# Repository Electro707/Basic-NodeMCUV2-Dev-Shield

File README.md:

# E707 Basic NodeMCU-V2 Shield 

This shield/daughterboard is for the NodeMCU V2 (also known as NodeMCU DevKit V1.0, kind of confusing) to allow a begineer to have some components to play around with. In this case, that includes a 7-segment display, an RGB LED (which is hooked up with the 7-segment display), and 3 pushbuttons.

### Arduino Library

The Arduino library for this shield can be found at: [https://github.com/Electro707/Basic-NodeMCUV2-Dev-Shield-Library](https://github.com/Electro707/Basic-NodeMCUV2-Dev-Shield-Library). It provides pin definitions and more importantly some examples to get started with.

The reason it's in a different repo is to allow for an easy download of the library as a ZIP file (using GitHub's "Download ZIP" option) to be easily imported into the Arduino IDE. 

### PCB

The PCB files can be found in the `KiCAD Files` folder. 

There are different folders for different PCB layouts. More details can be found in [KiCAD_Files/README.md](KiCAD_Files/README.md)

#### PCB Panel

There is a panel (not tested tough) of the PCB for mass-production:

##### NOTE: If you have KiCAD 5.1.9 or lower, the KiCAD files will not open as it was designed with KiCAD 5.99 (the alpha/beta version of KiCAD V6).

### Docs 
Coming Soon!

### Credits:
- Creator and Maintainer:
    - Electro707 (Jamal Bouajjaj)
- KiCAD NODEMCU V2 Symbol:
    - jdunmire -> [https://github.com/jdunmire/kicad-ESP8266](https://github.com/jdunmire/kicad-ESP8266)
- Some Icons:
    - Arduino's IDE Repo -> [https://github.com/arduino/Arduino/blob/master/build/shared/lib/theme/buttons.svg](https://github.com/arduino/Arduino/blob/master/build/shared/lib/theme/buttons.svg)

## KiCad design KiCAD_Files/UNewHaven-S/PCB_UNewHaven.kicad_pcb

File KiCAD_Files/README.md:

# KiCAD Files Versions

There are different folders in this directory, and they are different versions of this shield. The schematic is all the same, the difference lying in the PCB layout/footprints.

- Standard-S: The regular SMD version of the board, optimized for mass production.
- Standard-T: The regular THT version of the board, optimized to be used as a soldering kit.
- UNewHaven-S: The University of New Haven version, used for the school's "Welcome Kit" something. Optimized for mass production.

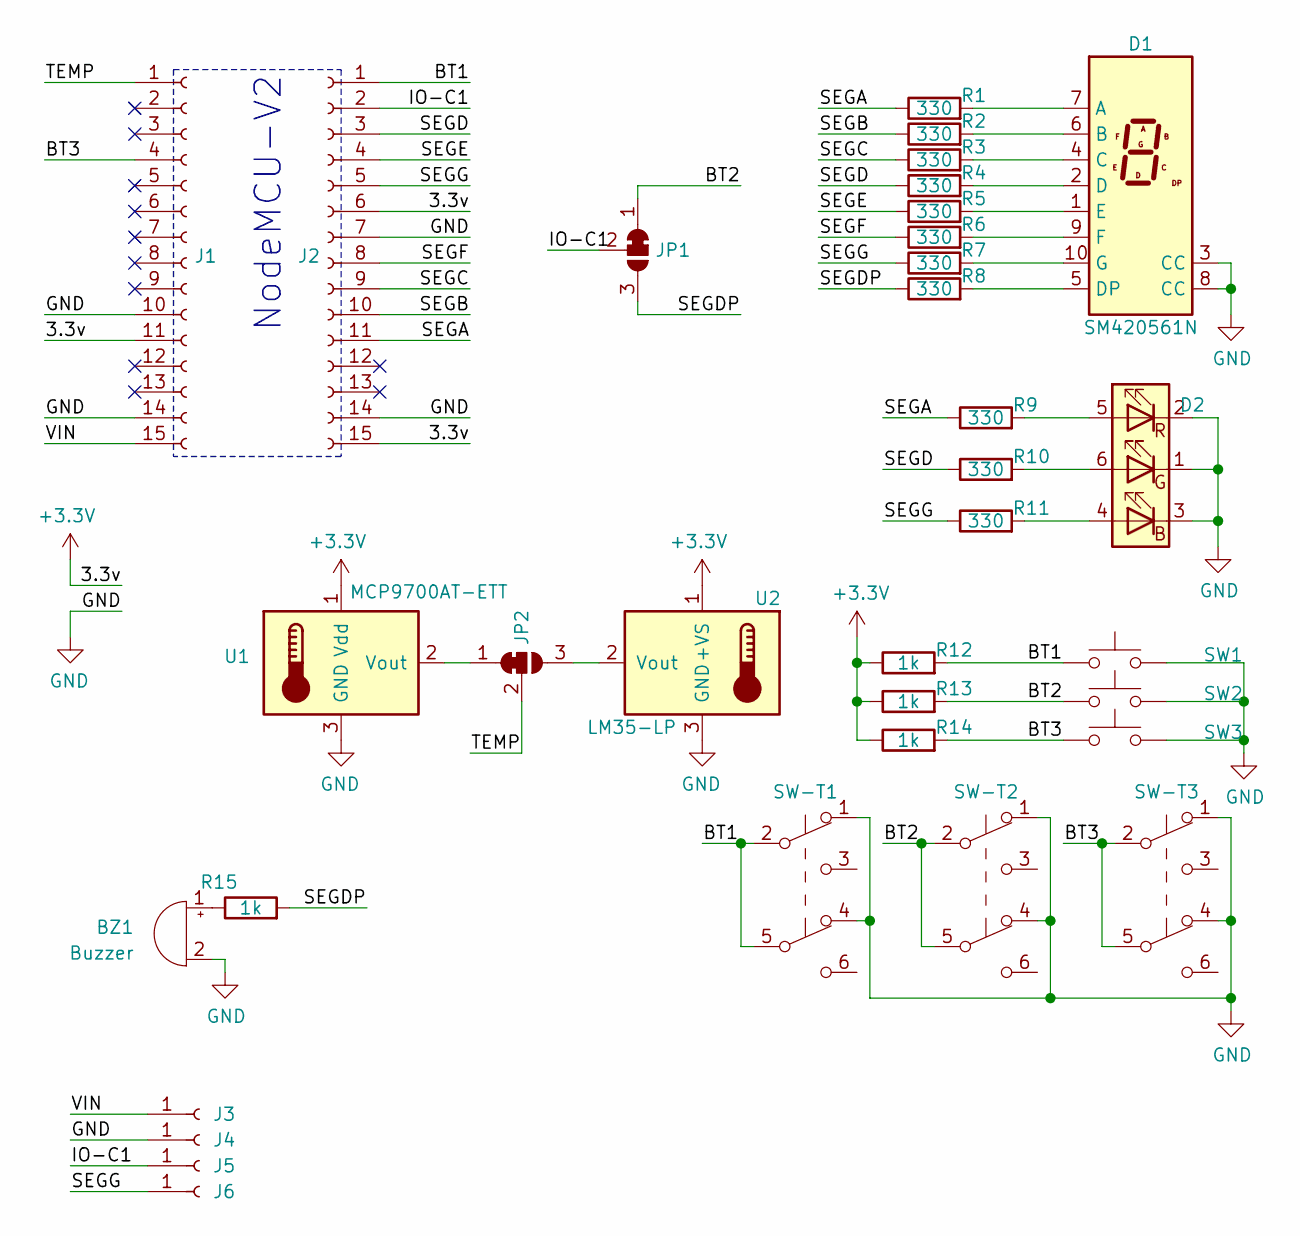
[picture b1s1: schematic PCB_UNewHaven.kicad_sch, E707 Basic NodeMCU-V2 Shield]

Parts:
BZ1: Buzzer; Buzzer_12x9.5RM7.6
D1: SM420561N; 7SegmentLED_LTS6760_LTS6780
D2: LED_RGB; LED_RGB_5050-6; LCSC C784540
J1, J2: Conn_01x15_Female; PinSocket_1x15_P2.54mm_Vertical
J3, J4, J5, J6: Conn_01x01_Female; SingleExternalWire
JP1, JP2: SolderJumper_3_Bridged12; SolderJumper-3_P1.3mm_Bridged12_Pad1.0x1.5mm
R1, R2, R3, R4, R5, R6, R7, R8, R9, R10, R11: 330; R_1206_3216Metric_Pad1.30x1.75mm_HandSolder
R12, R13, R14, R15: 1k; R_1206_3216Metric_Pad1.30x1.75mm_HandSolder
SW1, SW2, SW3: SW_Push; SW_Push_1P1T_NO_6x6mm_H9.5mm
SW-T1, SW-T2, SW-T3: SW_Push_DPDT; SW_CuK_JS202011CQN_DPDT_Straight
U1: MCP9700AT-ETT; SOT-23
U2: LM35-LP; TO-92L_Wide

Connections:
+3V3: J1.11, J2.6, J2.15, R12.1, R13.1, R14.1, U1.1 (Vdd), U2.1 (+VS)
/BT1: J2.1, R12.2, SW1.1, SW-T1.2 (B), SW-T1.5 (B)
/BT2: JP1.1 (A), R13.2, SW2.1, SW-T2.2 (B), SW-T2.5 (B)
/BT3: J1.4, R14.2, SW3.1, SW-T3.2 (B), SW-T3.5 (B)
/IO-C1: J2.2, J5.1, JP1.2 (C)
/SEGA: J2.11, R1.1, R9.1
/SEGB: J2.10, R2.1
/SEGC: J2.9, R3.1
/SEGD: J2.3, R4.1, R10.1
/SEGDP: JP1.3 (B), R8.1, R15.2
/SEGE: J2.4, R5.1
/SEGF: J2.8, R6.1
/SEGG: J2.5, J6.1, R7.1, R11.1
/TEMP: J1.1, JP2.2 (C)
/VIN: J1.15, J3.1
GND: BZ1.2 (+), D1.3 (CC), D1.8 (CC), D2.1 (GK), D2.2 (RK), D2.3 (BK), J1.10, J1.14, J2.7, J2.14, J4.1, SW1.2, SW2.2, SW3.2, SW-T1.1 (A), SW-T1.4 (A), SW-T2.1 (A), SW-T2.4 (A), SW-T3.1 (A), SW-T3.4 (A), U1.3 (GND), U2.3 (GND)
unnamed: BZ1.1 (-), R15.1
unnamed: D1.1 (E), R5.2
unnamed: D1.2 (D), R4.2
unnamed: D1.4 (C), R3.2
unnamed: D1.5 (DP), R8.2
unnamed: D1.6 (B), R2.2
unnamed: D1.7 (A), R1.2
unnamed: D1.9 (F), R6.2
unnamed: D1.10 (G), R7.2
unnamed: D2.4 (BA), R11.2
unnamed: D2.5 (RA), R9.2
unnamed: D2.6 (GA), R10.2
unnamed: JP2.1 (A), U1.2 (Vout)
unnamed: JP2.3 (B), U2.2 (Vout)

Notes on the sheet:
NodeMCU-V2

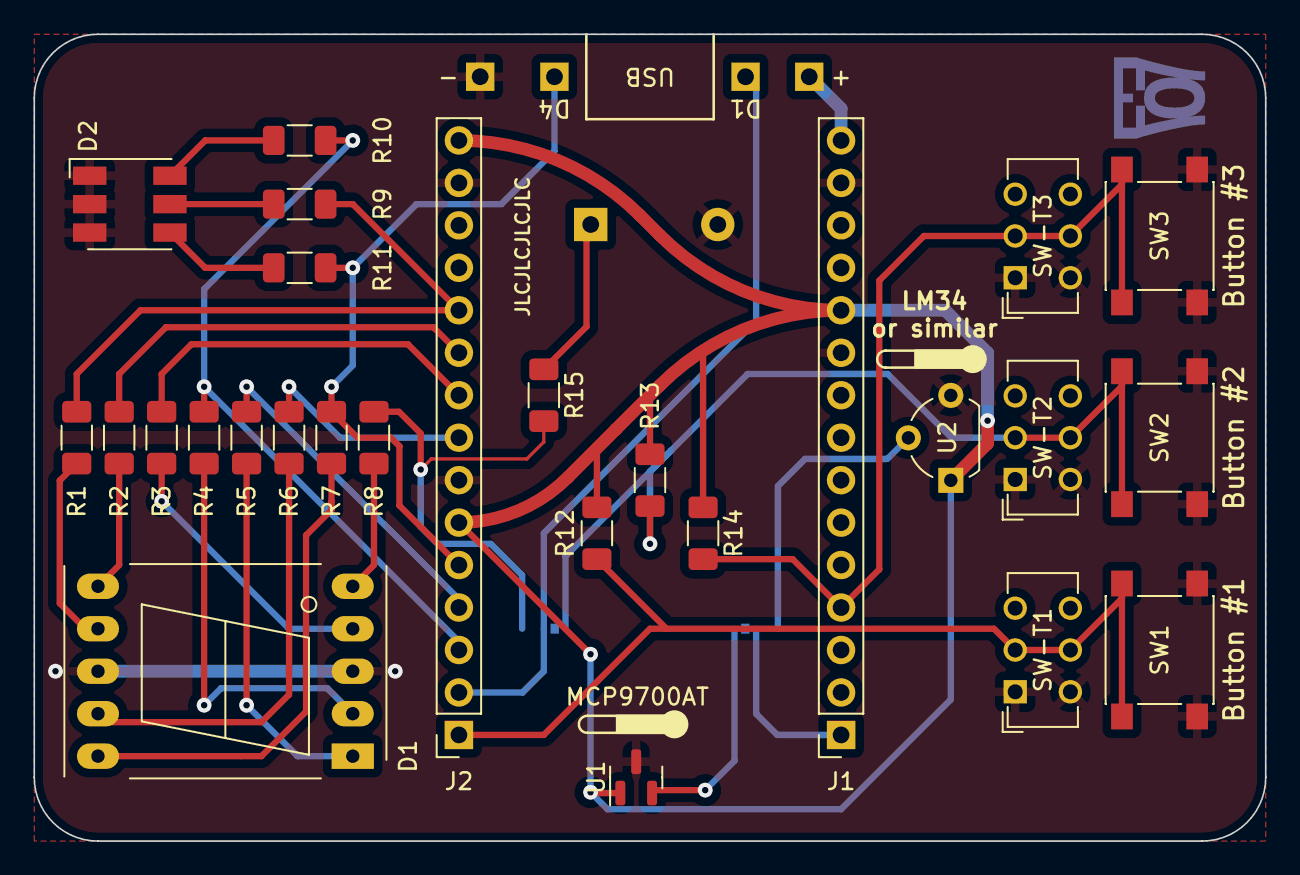
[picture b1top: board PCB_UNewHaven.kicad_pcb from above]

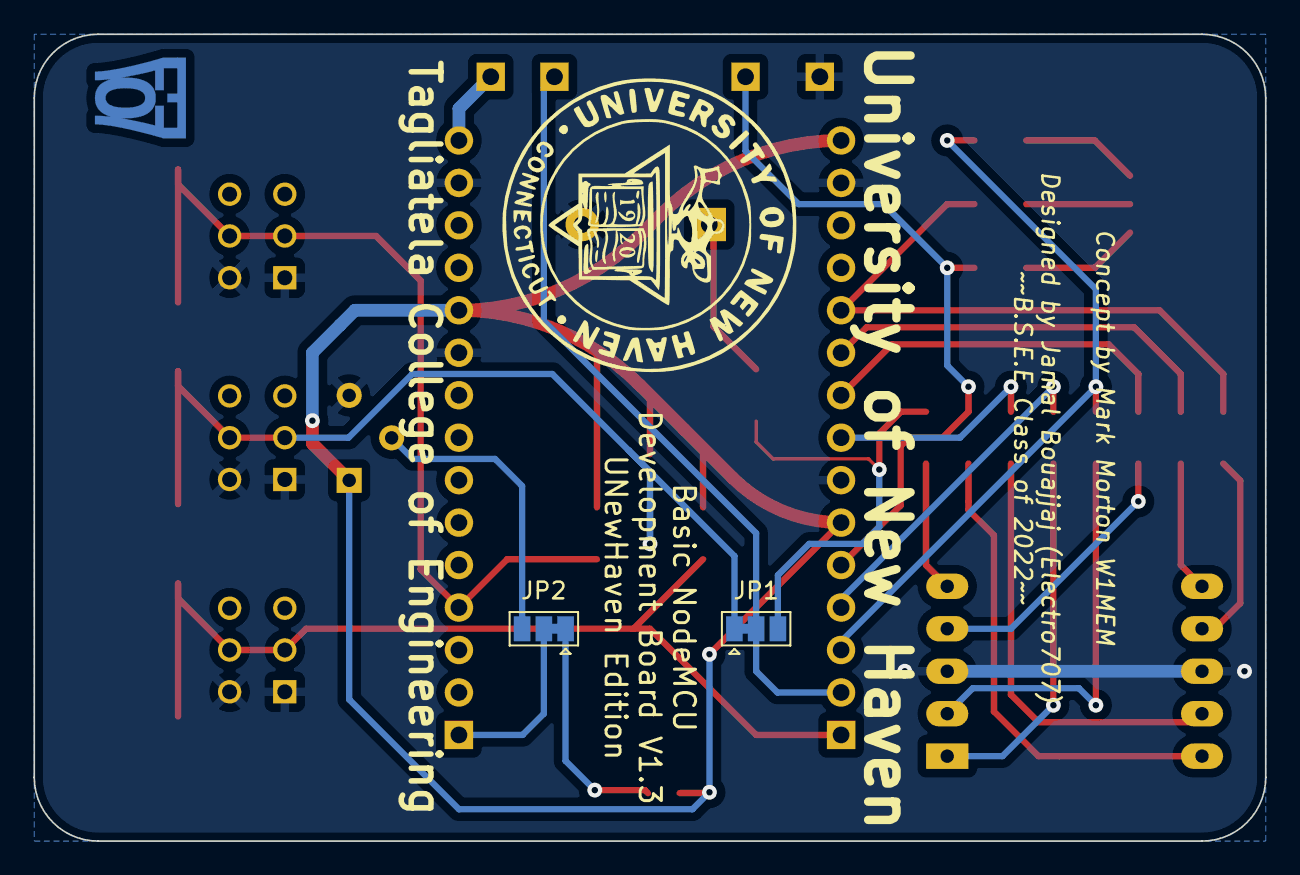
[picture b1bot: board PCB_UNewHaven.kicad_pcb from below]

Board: 2 copper layers, 73.7 x 48.3 mm, 36 parts (4 on the bottom side), 30 nets.

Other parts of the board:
Ref**: Val**; NPN_6x6mm
Ref**#2: Val**; NPN_6x6mm

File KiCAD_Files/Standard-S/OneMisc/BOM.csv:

Comment,Designator,Footprint,LCSC
SM420561N,D1,Display_7Segment:7SegmentLED_LTS6760_LTS6780,C141367
LED_RGB,D2,LED_SMD:LED_RGB_5050-6,C784540
Conn_01x15_Female,"J1,J2",Connector_PinSocket_2.54mm:PinSocket_1x15_P2.54mm_Vertical,C124408
330,"R1,R2,R3,R4,R5,R6,R7,R8,R9,R10,R11",Resistor_SMD:R_1206_3216Metric_Pad1.30x1.75mm_HandSolder,C17930
1k,"R12,R13,R14",Resistor_SMD:R_1206_3216Metric_Pad1.30x1.75mm_HandSolder,C4410
SW_Push,"SW1,SW2,SW3",Button_Switch_SMD:SW_Push_1P1T_NO_6x6mm_H9.5mm,C136669
MCP9700AT-ETT,U1,Package_TO_SOT_SMD:SOT-23,C127949

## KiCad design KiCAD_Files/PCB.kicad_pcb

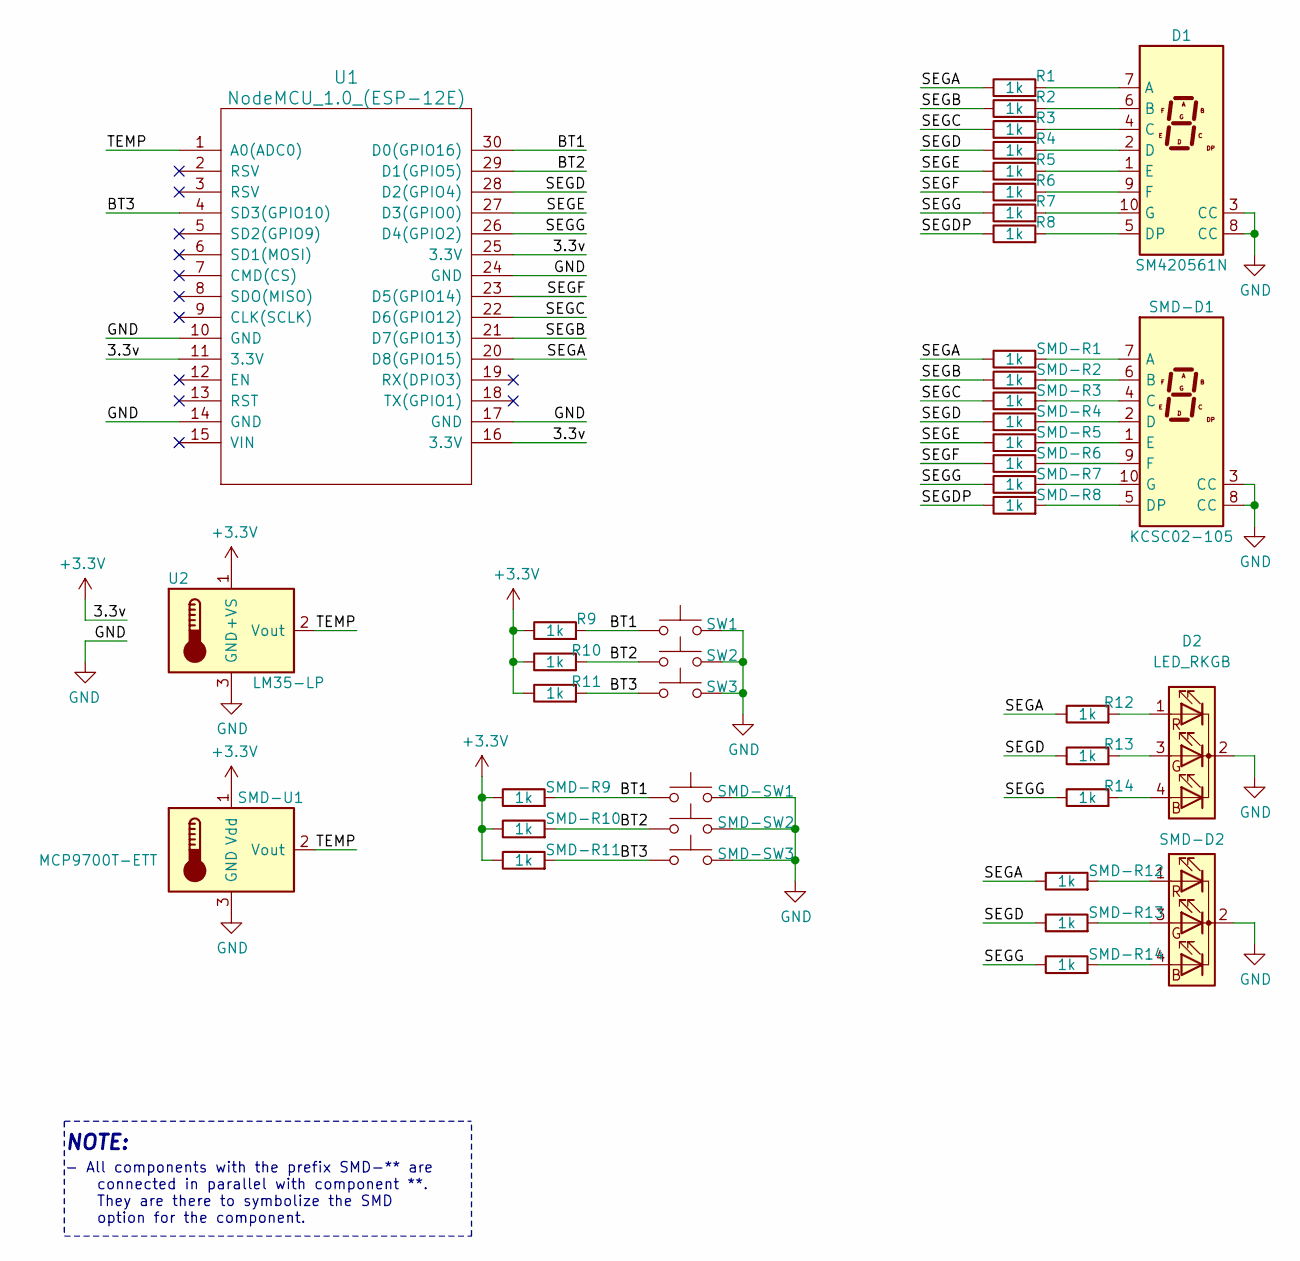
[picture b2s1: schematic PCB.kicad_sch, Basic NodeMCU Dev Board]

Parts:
D1: SM420561N; 7SegmentLED_LTS6760_LTS6780
D2: LED_RKGB; LED_D5.0mm-4_RGB_Staggered_Pins
R1, R2, R3, R4, R5, R6, R7, R8, R12, R13, R14: 1k; R_Axial_DIN0207_L6.3mm_D2.5mm_P7.62mm_Horizontal
R9, R10, R11: 1k; R_Axial_DIN0207_L6.3mm_D2.5mm_P10.16mm_Horizontal
SMD-D1: KCSC02-105
SMD-D2: LED_RKGB; LED_D5.0mm-4_RGB_Staggered_Pins
SMD-R1, SMD-R2, SMD-R3, SMD-R4, SMD-R5, SMD-R6, SMD-R7, SMD-R8, SMD-R9, SMD-R10, SMD-R11, SMD-R12, SMD-R13, SMD-R14: 1k; R_1206_3216Metric_Pad1.30x1.75mm_HandSolder
SMD-SW1, SMD-SW2, SMD-SW3: SW_Push; SW_Push_1P1T_NO_6x6mm_H9.5mm
SMD-U1: MCP9700T-ETT; SOT-23
SW1, SW2, SW3: SW_Push; SW_PUSH_6mm
U1: NodeMCU_1.0_(ESP-12E); NodeMCU V2
U2: LM35-LP; TO-92L_Wide

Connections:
+3V3: R9.1, R10.1, R11.1, SMD-R9.1, SMD-R10.1, SMD-R11.1, SMD-U1.1 (Vdd), U1.11 (3.3V), U1.16 (3.3V), U1.25 (3.3V), U2.1 (+VS)
/BT1: R9.2, SMD-R9.2, SMD-SW1.1, SW1.1, U1.30 (D0(GPIO16))
/BT2: R10.2, SMD-R10.2, SMD-SW2.1, SW2.1, U1.29 (D1(GPIO5))
/BT3: R11.2, SMD-R11.2, SMD-SW3.1, SW3.1, U1.4 (SD3(GPIO10))
/SEGA: R1.1, R12.1, SMD-R1.1, SMD-R12.1, U1.20 (D8(GPIO15))
/SEGB: R2.1, SMD-R2.1, U1.21 (D7(GPIO13))
/SEGC: R3.1, SMD-R3.1, U1.22 (D6(GPIO12))
/SEGD: R4.1, R13.1, SMD-R4.1, SMD-R13.1, U1.28 (D2(GPIO4))
/SEGDP: R8.1, SMD-R8.1
/SEGE: R5.1, SMD-R5.1, U1.27 (D3(GPIO0))
/SEGF: R6.1, SMD-R6.1, U1.23 (D5(GPIO14))
/SEGG: R7.1, R14.1, SMD-R7.1, SMD-R14.1, U1.26 (D4(GPIO2))
/TEMP: SMD-U1.2 (Vout), U1.1 (A0(ADC0)), U2.2 (Vout)
GND: D1.3 (CC), D1.8 (CC), D2.2 (K), SMD-D1.3 (CC), SMD-D1.8 (CC), SMD-D2.2 (K), SMD-SW1.2, SMD-SW2.2, SMD-SW3.2, SMD-U1.3 (GND), SW1.2, SW2.2, SW3.2, U1.10 (GND), U1.14 (GND), U1.17 (GND), U1.24 (GND), U2.3 (GND)
unnamed: D1.1 (E), R5.2
unnamed: D1.2 (D), R4.2
unnamed: D1.4 (C), R3.2
unnamed: D1.5 (DP), R8.2
unnamed: D1.6 (B), R2.2
unnamed: D1.7 (A), R1.2
unnamed: D1.9 (F), R6.2
unnamed: D1.10 (G), R7.2
unnamed: D2.1 (RA), R12.2
unnamed: D2.3 (GA), R13.2
unnamed: D2.4 (BA), R14.2
unnamed: SMD-D1.1 (E), SMD-R5.2
unnamed: SMD-D1.2 (D), SMD-R4.2
unnamed: SMD-D1.4 (C), SMD-R3.2
unnamed: SMD-D1.5 (DP), SMD-R8.2
unnamed: SMD-D1.6 (B), SMD-R2.2
unnamed: SMD-D1.7 (A), SMD-R1.2
unnamed: SMD-D1.9 (F), SMD-R6.2
unnamed: SMD-D1.10 (G), SMD-R7.2
unnamed: SMD-D2.1 (RA), SMD-R12.2
unnamed: SMD-D2.3 (GA), SMD-R13.2
unnamed: SMD-D2.4 (BA), SMD-R14.2

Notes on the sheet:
NOTE:
- All components with the prefix SMD-** are connected in parallel with component **. They are there to symbolize the SMD option for the component.

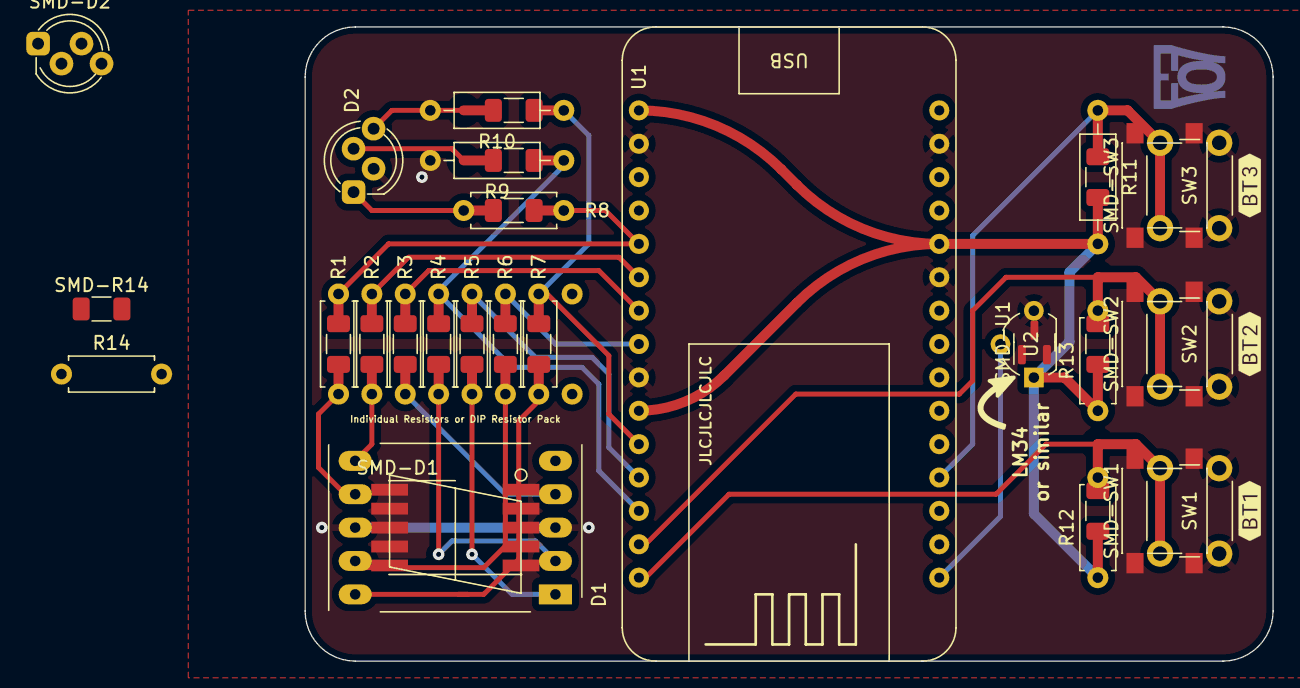
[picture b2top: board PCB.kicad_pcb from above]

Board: 2 copper layers, 73.7 x 48.3 mm, 43 parts (1 on the bottom side), 36 nets.

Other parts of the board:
Ref**: Val**; NPN_6x6mm
Ref**#2: Val**; NPN_6x6mm

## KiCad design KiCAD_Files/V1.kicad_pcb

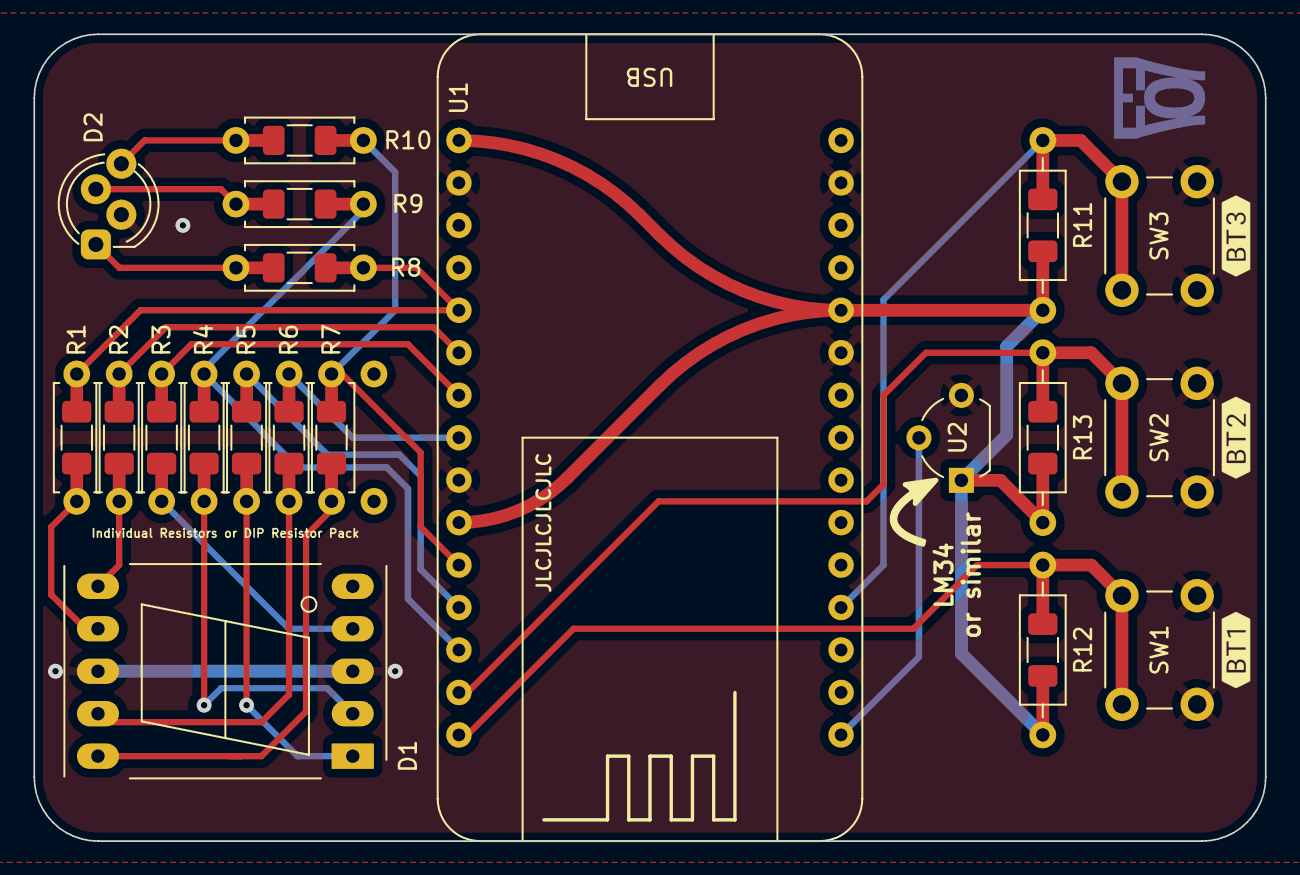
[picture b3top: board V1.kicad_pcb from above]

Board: 2 copper layers, 73.7 x 48.3 mm, 35 parts (1 on the bottom side), 23 nets.

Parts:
D1: SM420561N; 7SegmentLED_LTS6760_LTS6780
D2: LED_RKGB; LED_D5.0mm-4_RGB_Staggered_Pins
R1, R2, R3, R4, R5, R6, R7, R8, R9, R10: 1k; R_Axial_DIN0207_L6.3mm_D2.5mm_P7.62mm_Horizontal
R11, R12, R13: 1k; R_Axial_DIN0207_L6.3mm_D2.5mm_P10.16mm_Horizontal
Ref**: Val**; NPN_6x6mm
Ref**#2: Val**; NPN_6x6mm
SMD-R1, SMD-R2, SMD-R3, SMD-R4, SMD-R5, SMD-R6, SMD-R7, SMD-R8, SMD-R9, SMD-R10, SMD-R11, SMD-R12, SMD-R13: 1k; R_1206_3216Metric_Pad1.30x1.75mm_HandSolder
SW1, SW2, SW3: SW_Push; SW_PUSH_6mm
U1: NodeMCU_1.0_(ESP-12E); NodeMCU V2
U2: LM35-LP; TO-92L_Wide

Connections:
+3V3: R11.1, R12.1, R13.1, SMD-R11.2, SMD-R12.2, SMD-R13.2, U1.11 (3.3V), U1.16 (3.3V), U1.25 (3.3V), U2.1 (+VS)
/BT1: R12.2, SMD-R12.1, SW1.1, U1.30 (D0(GPIO16))
/BT2: R13.2, SMD-R13.1, SW2.1, U1.29 (D1(GPIO5))
/BT3: R11.2, SMD-R11.1, SW3.1, U1.4 (SD3(GPIO10))
/SEGA: R1.1, R8.1, SMD-R1.1, SMD-R8.1, U1.20 (D8(GPIO15))
/SEGB: R2.1, SMD-R2.1, U1.21 (D7(GPIO13))
/SEGC: R3.1, SMD-R3.1, U1.22 (D6(GPIO12))
/SEGD: R4.1, R9.1, SMD-R4.1, SMD-R9.1, U1.28 (D2(GPIO4))
/SEGE: R5.1, SMD-R5.1, U1.27 (D3(GPIO0))
/SEGF: R6.1, SMD-R6.1, U1.23 (D5(GPIO14))
/SEGG: R7.1, R10.1, SMD-R7.1, SMD-R10.1, U1.26 (D4(GPIO2))
/TEMP: U1.1 (A0(ADC0)), U2.2 (Vout)
GND: D1.3 (CC), D1.8 (CC), D2.2 (K), SW1.2, SW2.2, SW3.2, U1.10 (GND), U1.14 (GND), U1.17 (GND), U1.24 (GND), U2.3 (GND)
unnamed: D1.1 (E), R5.2, SMD-R5.2
unnamed: D1.2 (D), R4.2, SMD-R4.2
unnamed: D1.4 (C), R3.2, SMD-R3.2
unnamed: D1.6 (B), R2.2, SMD-R2.2
unnamed: D1.7 (A), R1.2, SMD-R1.2
unnamed: D1.9 (F), R6.2, SMD-R6.2
unnamed: D1.10 (G), R7.2, SMD-R7.2
unnamed: D2.1 (RA), R8.2, SMD-R8.2
unnamed: D2.3 (GA), R9.2, SMD-R9.2
unnamed: D2.4 (BA), R10.2, SMD-R10.2

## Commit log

2021-03-10 Updated Schematic. Started a Getting Started guide
2021-03-10 Changed name in docs. Added some Arduino icons
2021-03-10 Some docs changes. Added preview image
2021-03-12 Added TODO list for next rev
2021-03-15 Added .net file. Changed origin. Last commit for V1 PCB
2021-03-15 Changed PCB design name to PCB instead of V1
2021-03-15 Started working on V1.1 of the PCB. Many more changes needed
2021-03-15 Some residual changes from last commit
2021-03-17 Pushing Version 1.1, all 3 versions of it
2021-03-17 Removed the preliminary part of the getting started docs, as it should be for the most part off egnough. More changes to docs
2021-03-18 Added Panelization files and stuff
2021-04-14 UNewHaven Version 1.2 Update. Removed project from pre-release in README.md
2021-04-20 Added new pic. Changed README.md
2021-10-07 Almost finished Rev1.3 of the UNewHaven board
2022-01-23 Added some external pin headers
2022-02-11 Changed the external pinout's connectors. Minor silk changes. DRC fixes
2022-02-14 Added LCSC component attributes
2025-06-29 Some unknown prl and pro changes?
2025-06-29 Added some 'released' files
